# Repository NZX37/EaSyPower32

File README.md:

# EaSyPower32

EaSyPower32 is an ESP32-S3 development board with USB-C and a connection for a TP4056 charger module. It is designed to make battery-powered ESP32 projects easier to prototype.

## Features

- ESP32-S3-WROOM-1 module (N16R2)
- USB-C connection
- AP2112K 3.3 V regulator
- Reset and boot buttons
- Status LED and SK6812 RGB LED
- Breakout pins for connecting a TP4056 charger module

The TP4056 itself is not included on the PCB; install a compatible charger module in the board's battery-power connection.

## Design files

KiCad source files are in [`kicad files/`](kicad%20files/). The schematic and board previews are shown below.

| Schematic | PCB layout | Board view |
| --- | --- | --- |
|  |  |  |

## Manufacturing

Ready-to-upload Gerber and drill files are in [`Production Files/`](Production%20Files/). The original fabrication bundle is [`EaSyPower32_v1.zip`](Production%20Files/EaSyPower32_v1.zip). It contains the copper, solder mask, paste, silkscreen, board outline, and plated/non-plated drill files. The matching BOM and placement files are included as CSVs in the same folder.

For a new or modified board revision, open `breadESP32.kicad_pcb` in KiCad and regenerate fabrication outputs from that board before ordering. Check the board outline and manufacturer design rules against your chosen fabricator.

## Bill of materials

Assembly quantities are for one board and match the [assembly BOM](Production%20Files/EaSyPower32_v1_bom.csv). Unit prices vary with order quantity and stock; each LCSC listing shows the current price.

| Part / reference(s) | Quantity | Unit price | Buying link |
| --- | ---: | ---: | --- |
| 10 µF capacitor, C2/C5/C13 | 3 | See listing | [LCSC C49678](https://www.lcsc.com/product-detail/C49678.html) |
| 1 µF capacitor, C3/C4/C11 | 3 | See listing | [LCSC C5199872](https://www.lcsc.com/product-detail/C5199872.html) |
| 100 nF capacitor, C6/C7/C8/C12 | 4 | See listing | [LCSC C14663](https://www.lcsc.com/product-detail/C14663.html) |
| 1N5819WS Schottky diode, D1 | 1 | See listing | [LCSC C5451629](https://www.lcsc.com/product-detail/C5451629.html) |
| TVS diode, D2/D3/D4 | 3 | See listing | [LCSC C7519](https://www.lcsc.com/product-detail/C7519.html) |
| Indicator LED, D5 | 1 | See listing | [LCSC C19171390](https://www.lcsc.com/product-detail/C19171390.html) |
| SK6812 RGB LED, D6 | 1 | See listing | [LCSC C5378720](https://www.lcsc.com/product-detail/C5378720.html) |
| USB-C receptacle, J1 | 1 | See listing | [LCSC C165948](https://www.lcsc.com/product-detail/C165948.html) |
| 5.1 kΩ resistor, R2/R3 | 2 | See listing | [LCSC C2907044](https://www.lcsc.com/product-detail/C2907044.html) |
| 75 Ω resistor, R4 | 1 | See listing | [LCSC C17820](https://www.lcsc.com/product-detail/C17820.html) |
| 10 kΩ resistor, R5/R6/R7 | 3 | See listing | [LCSC C98220](https://www.lcsc.com/product-detail/C98220.html) |
| Tactile push button, SW1/SW2 | 2 | See listing | [LCSC C273499](https://www.lcsc.com/product-detail/C273499.html) |
| AP2112K-3.3 regulator, U1 | 1 | See listing | [LCSC C51118](https://www.lcsc.com/product-detail/C51118.html) |
| ESP32-S3-WROOM-1-N16R2, U3 | 1 | See listing | [LCSC C2913205](https://www.lcsc.com/product-detail/C2913205.html) |

See [`BOM.md`](BOM.md) for the full component list. The TP4056 charger module is external and is not included in this assembly BOM. The project journal is in [`JOURNAL.md`](JOURNAL.md), and the `Firmware/` folder contains a minimal Arduino sketch.

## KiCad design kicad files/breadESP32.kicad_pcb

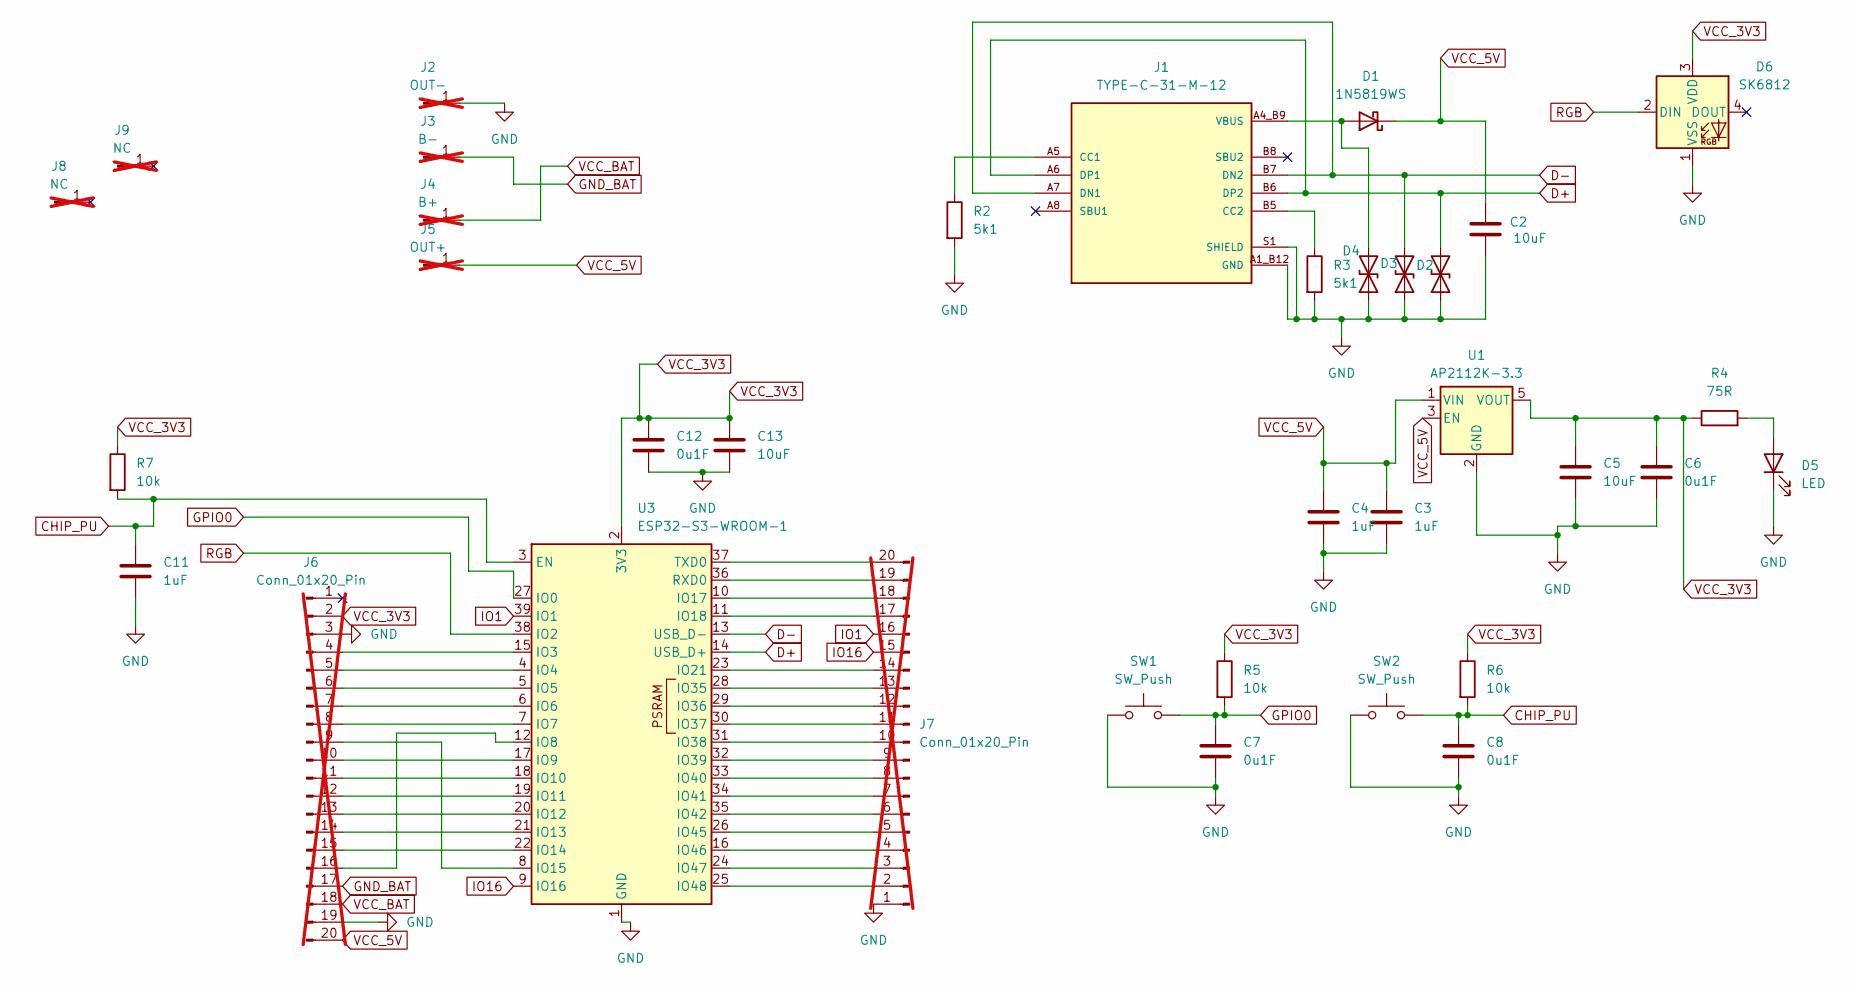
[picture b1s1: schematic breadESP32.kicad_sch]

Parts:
C2, C5, C13: 10uF; C_0805_2012Metric_Pad1.18x1.45mm_HandSolder; LCSC C49678
C3, C4, C11: 1uF; C_0805_2012Metric_Pad1.18x1.45mm_HandSolder; LCSC C5199872
C6, C7, C8, C12: 0u1F; C_0603_1608Metric_Pad1.08x0.95mm_HandSolder; LCSC C14663
D1: 1N5819WS; D_SOD-323_HandSoldering; LCSC C5451629
D2, D3, D4: D_TVS; D_SOD-323_HandSoldering; LCSC C7519
D5: LED; LED_0603_1608Metric_Pad1.05x0.95mm_HandSolder; LCSC C19171390
D6: SK6812; LED_SK6812_PLCC4_5.0x5.0mm_P3.2mm; LCSC C5378720
J1: TYPE-C-31-M-12; HRO_TYPE-C-31-M-12; PARTREV 2020.12.08; LCSC C165948
J2: OUT-; PinHeader_1x01_P2.54mm_Vertical; not fitted
J3: B-; PinHeader_1x01_P2.54mm_Vertical; not fitted
J4: B+; PinHeader_1x01_P2.54mm_Vertical; not fitted
J5: OUT+; PinHeader_1x01_P2.54mm_Vertical; not fitted
J6, J7: Conn_01x20_Pin; PinHeader_1x20_P2.54mm_Vertical; not fitted
J8, J9: NC; PinHeader_1x01_P2.54mm_Vertical; not fitted
R2, R3: 5k1; R_0603_1608Metric_Pad0.98x0.95mm_HandSolder; LCSC C2907044
R4: 75R; R_0805_2012Metric_Pad1.20x1.40mm_HandSolder; LCSC C17820
R5, R6, R7: 10k; R_0603_1608Metric_Pad0.98x0.95mm_HandSolder; LCSC C98220
SW1, SW2: SW_Push; SW_SPST_B3S-1000; LCSC C273499
U1: AP2112K-3.3; SOT-23-5; LCSC C51118
U3: ESP32-S3-WROOM-1; LCSC C2913205

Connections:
CHIP_PU: C8.1, C11.1, R6.2, R7.2, SW2.2, U3.3 (EN)
D+: D2.2 (A2), J1.A6 (DP1), J1.B6 (DP2), U3.14 (USB_D+)
D-: D3.2 (A2), J1.A7 (DN1), J1.B7 (DN2), U3.13 (USB_D-)
GND: C2.2, C3.2, C4.2, C5.2, C6.2, C7.2, C8.2, C11.2, C12.2, C13.2, D2.1 (A1), D3.1 (A1), D4.1 (A1), D5.1 (K), D6.1 (VSS), J1.A1_B12 (GND), J1.B1_A12 (GND), J1.S1 (SHIELD), J1.S2 (SHIELD), J1.S3 (SHIELD), J1.S4 (SHIELD), J2.1 (Pin_1_1), J6.3, J6.19, J7.1, R2.2, R3.2, SW1.1, SW2.1, U1.2 (GND), U3.1 (GND), U3.40 (GND), U3.41 (GND)
GND_BAT: J3.1 (Pin_1_1), J6.17
GPIO0: C7.1, R5.2, SW1.2, U3.27 (IO0)
IO1: J7.16, U3.39 (IO1)
IO16: J7.15, U3.9 (IO16)
unnamed: D5.2 (A), R4.2
unnamed: J1.A5 (CC1), R2.1
unnamed: J1.B5 (CC2), R3.1
unnamed: J6.4, U3.15 (IO3)
unnamed: J6.5, U3.4 (IO4)
unnamed: J6.6, U3.5 (IO5)
unnamed: J6.7, U3.6 (IO6)
unnamed: J6.8, U3.7 (IO7)
unnamed: J6.9, U3.8 (IO15)
unnamed: J6.10, U3.17 (IO9)
unnamed: J6.11, U3.18 (IO10)
unnamed: J6.12, U3.19 (IO11)
unnamed: J6.13, U3.20 (IO12)
unnamed: J6.14, U3.21 (IO13)
unnamed: J6.15, U3.22 (IO14)
unnamed: J6.16, U3.12 (IO8)
unnamed: J7.2, U3.25 (IO48)
unnamed: J7.3, U3.24 (IO47)
unnamed: J7.4, U3.16 (IO46)
unnamed: J7.5, U3.26 (IO45)
unnamed: J7.6, U3.35 (IO42)
unnamed: J7.7, U3.34 (IO41)
unnamed: J7.8, U3.33 (IO40)
unnamed: J7.9, U3.32 (IO39)
unnamed: J7.10, U3.31 (IO38)
unnamed: J7.11, U3.30 (IO37)
unnamed: J7.12, U3.29 (IO36)
unnamed: J7.13, U3.28 (IO35)
unnamed: J7.14, U3.23 (IO21)
unnamed: J7.17, U3.11 (IO18)
unnamed: J7.18, U3.10 (IO17)
unnamed: J7.19, U3.36 (RXD0)
unnamed: J7.20, U3.37 (TXD0)
RGB: D6.2 (DIN), U3.38 (IO2)
VBUS: D1.2 (A), D4.2 (A2), J1.A4_B9 (VBUS), J1.B4_A9 (VBUS)
VCC_3V3: C5.1, C6.1, C12.1, C13.1, D6.3 (VDD), J6.2, R4.1, R5.1, R6.1, R7.1, U1.5 (VOUT), U3.2 (3V3)
VCC_5V: C2.1, C3.1, C4.1, D1.1 (K), J5.1 (Pin_1_1), J6.20, U1.1 (VIN), U1.3 (EN)
VCC_BAT: J4.1 (Pin_1_1), J6.18

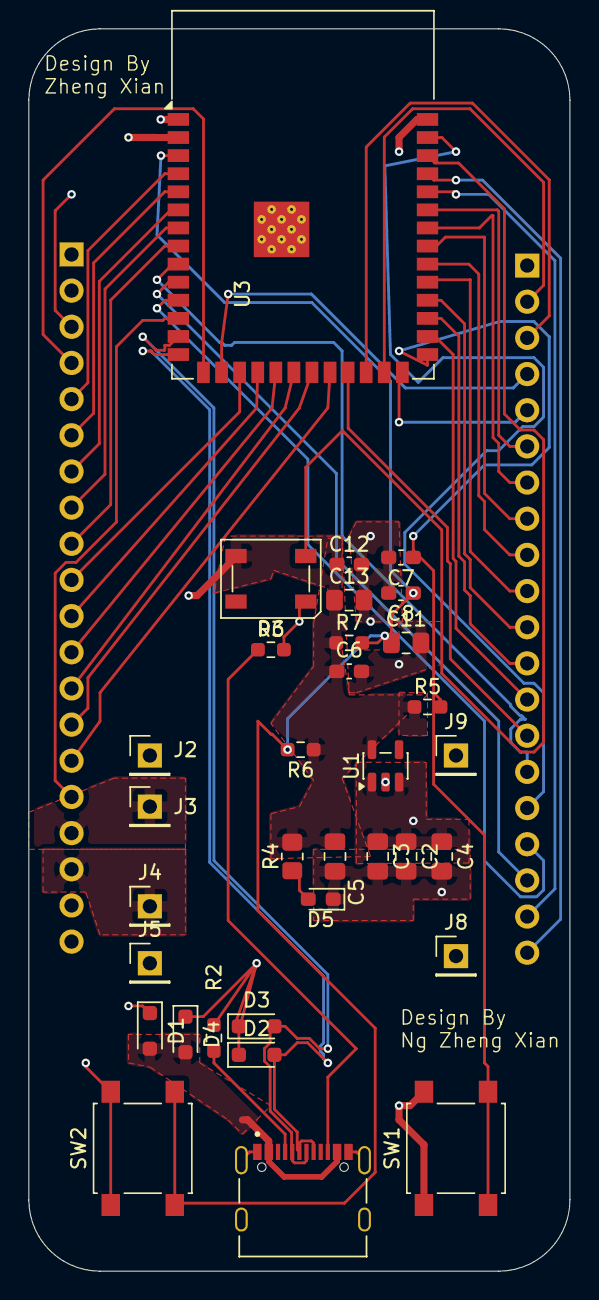
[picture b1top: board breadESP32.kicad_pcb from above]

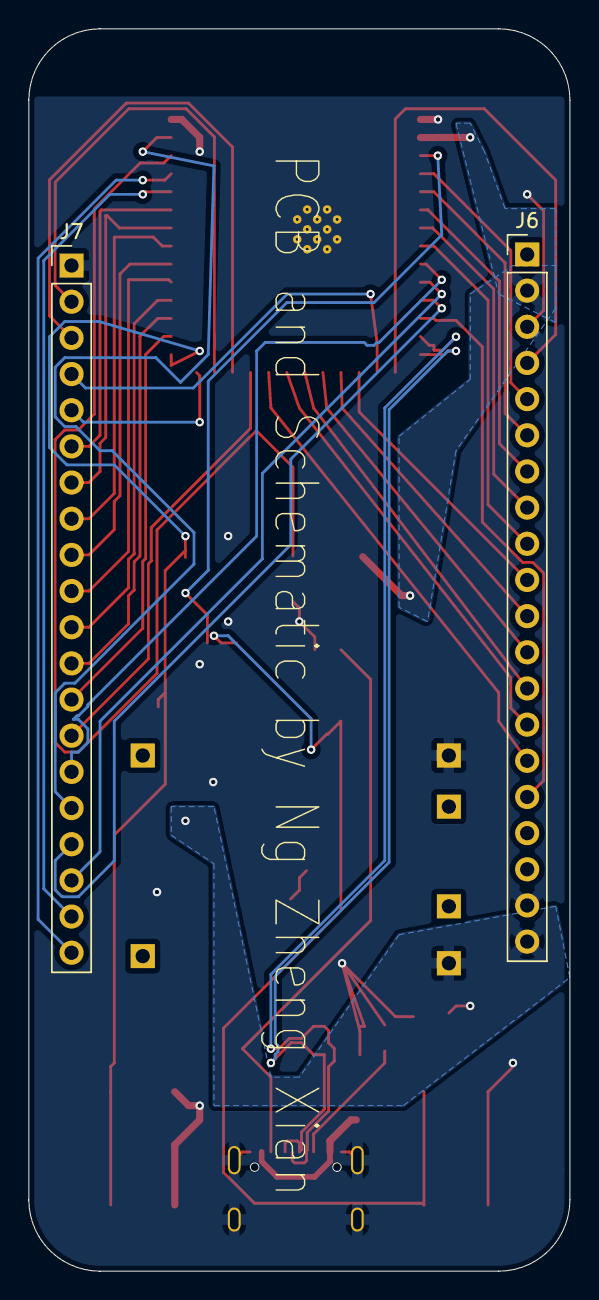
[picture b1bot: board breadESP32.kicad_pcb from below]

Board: 2 copper layers, 38.0 x 87.2 mm, 35 parts (2 on the bottom side), 46 nets.

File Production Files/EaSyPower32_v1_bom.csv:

Designator,Footprint,Quantity,Value,LCSC Part #
"C11, C3, C4",0805,3,1uF,C5199872
"C12, C6, C7, C8",0603,4,0u1F,C14663
"C13, C2, C5",0805,3,10uF,C49678
D1,D_SOD-323_HandSoldering,1,1N5819WS,C5451629 
"D2, D3, D4",D_SOD-323_HandSoldering,3,D_TVS,C7519 
D5,0603,1,LED,C19171390
D6,LED_SK6812_PLCC4_5.0x5.0mm_P3.2mm,1,SK6812,C5378720
J1,HRO_TYPE-C-31-M-12,1,TYPE-C-31-M-12,C165948
"R2, R3",0603,2,5k1,C2907044
R4,0805,1,75R,C17820
"R5, R6, R7",0603,3,10k,C98220
"SW1, SW2",SW_SPST_B3S-1000,2,SW_Push,C273499
U1,SOT-23-5,1,AP2112K-3.3,C51118
U3,ESP32-S3-WROOM-1,1,ESP32-S3-WROOM-1,C2913205
